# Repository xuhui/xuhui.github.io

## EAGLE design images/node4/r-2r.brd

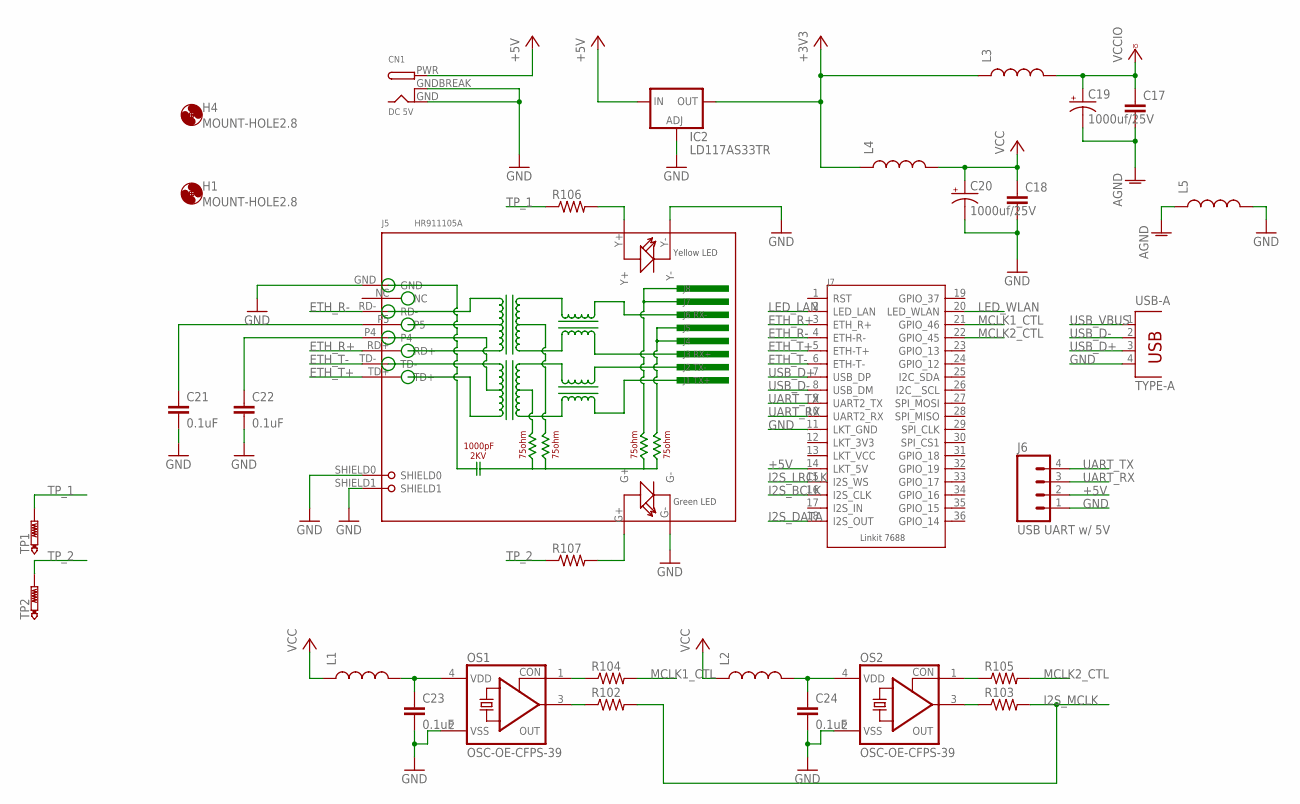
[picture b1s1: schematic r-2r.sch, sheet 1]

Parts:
C17, C18: CAPPTH1; CAP-PTH-5MM
C19, C20: 1000uf/25V; CPOL-RADIAL-1000UF-25V-KIT
C21, C22, C23, C24: 0.1uF; 0603-CAP
CN1: DC 5V; DCJACK_2MM_PTH
H1, H4: MOUNT-HOLE2.8; 2,8
IC2: LD117AS33TR; SOT223
J5: HR911105A; RJ45-12+2P-21.3X16.04X13.4MM
J6: USB UART w/ 5V; 1X04
J7: LINKIT-7688; LINKIT-7688-2X18
L1, L2, L5: INDUCTOR0603; 0603
L3, L4: INDUCTORAXIAL-0.6; AXIAL-0.6
OS1, OS2: OSC-OE-CFPS-39; 3.4X2.7-4-PAD
R102, R103, R104, R105, R106, R107: RESISTOR0603-RES; 0603-RES
TP1, TP2: PTR1PAD1-13; P1-13
USB-A: TYPE-A; PN87520

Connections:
+3V3: IC2.4 (OUT), L3.P$1 (1), L4.P$1 (1)
+5V: CN1.PWR, IC2.3 (IN), J6.2, J7.14 (LKT_5V)
AGND: C17.2, C19.-, L5.1; also elsewhere on the board
ETH_R+: J5.RD+, J7.3 (ETH_R+)
ETH_R-: J5.RD-, J7.4 (ETH-R-)
ETH_T+: J5.TD+, J7.5 (ETH-T+)
ETH_T-: J5.TD-, J7.6 (ETH-T-)
GND: C18.2, C20.-, C21.2, C22.2, C23.2, C24.2, CN1.GND, CN1.GNDBREAK, IC2.1 (ADJ), J5.G-, J5.GND, J5.SHIELD0, J5.SHIELD1, J5.Y-, J6.1, J7.11 (LKT_GND), L5.2, OS1.2 (VSS), OS2.2 (VSS), USB-A.4; also elsewhere on the board
I2S_BCLK: J7.16 (I2S_CLK); also elsewhere on the board
I2S_DATA: J7.18 (I2S_OUT); also elsewhere on the board
I2S_LRCLK: J7.15 (I2S_WS); also elsewhere on the board
I2S_MCLK: R102.2, R103.2; also elsewhere on the board
LED_LAN: J7.2 (LED_LAN)
LED_WLAN: J7.20 (LED_WLAN)
MCLK1_CTL: J7.21 (GPIO_46), R104.2
MCLK2_CTL: J7.22 (GPIO_45), R105.2
unnamed: C24.1, L2.2, OS2.4 (VDD)
unnamed: OS2.3 (OUT), R103.1
unnamed: OS1.3 (OUT), R102.1
unnamed: OS1.1 (CON), R104.1
unnamed: OS2.1 (CON), R105.1
unnamed: C23.1, L1.2, OS1.4 (VDD)
unnamed: J5.G+, R107.2
unnamed: J5.Y+, R106.2
unnamed: C22.1, J5.P4
unnamed: C21.1, J5.P5
TP_1: R106.1, TP1.TP
TP_2: R107.1, TP2.TP
UART_RX: J6.3, J7.10 (UART2_RX)
UART_TX: J6.4, J7.9 (UART2_TX)
USB_D+: J7.7 (USB_DP), USB-A.3
USB_D-: J7.8 (USB_DM), USB-A.2
USB_VBUS: USB-A.1
VCC: C18.1, C20.+, L1.1, L2.1, L4.P$2 (2); also elsewhere on the board
VCCIO: C17.1, C19.+, L3.P$2 (2); also elsewhere on the board

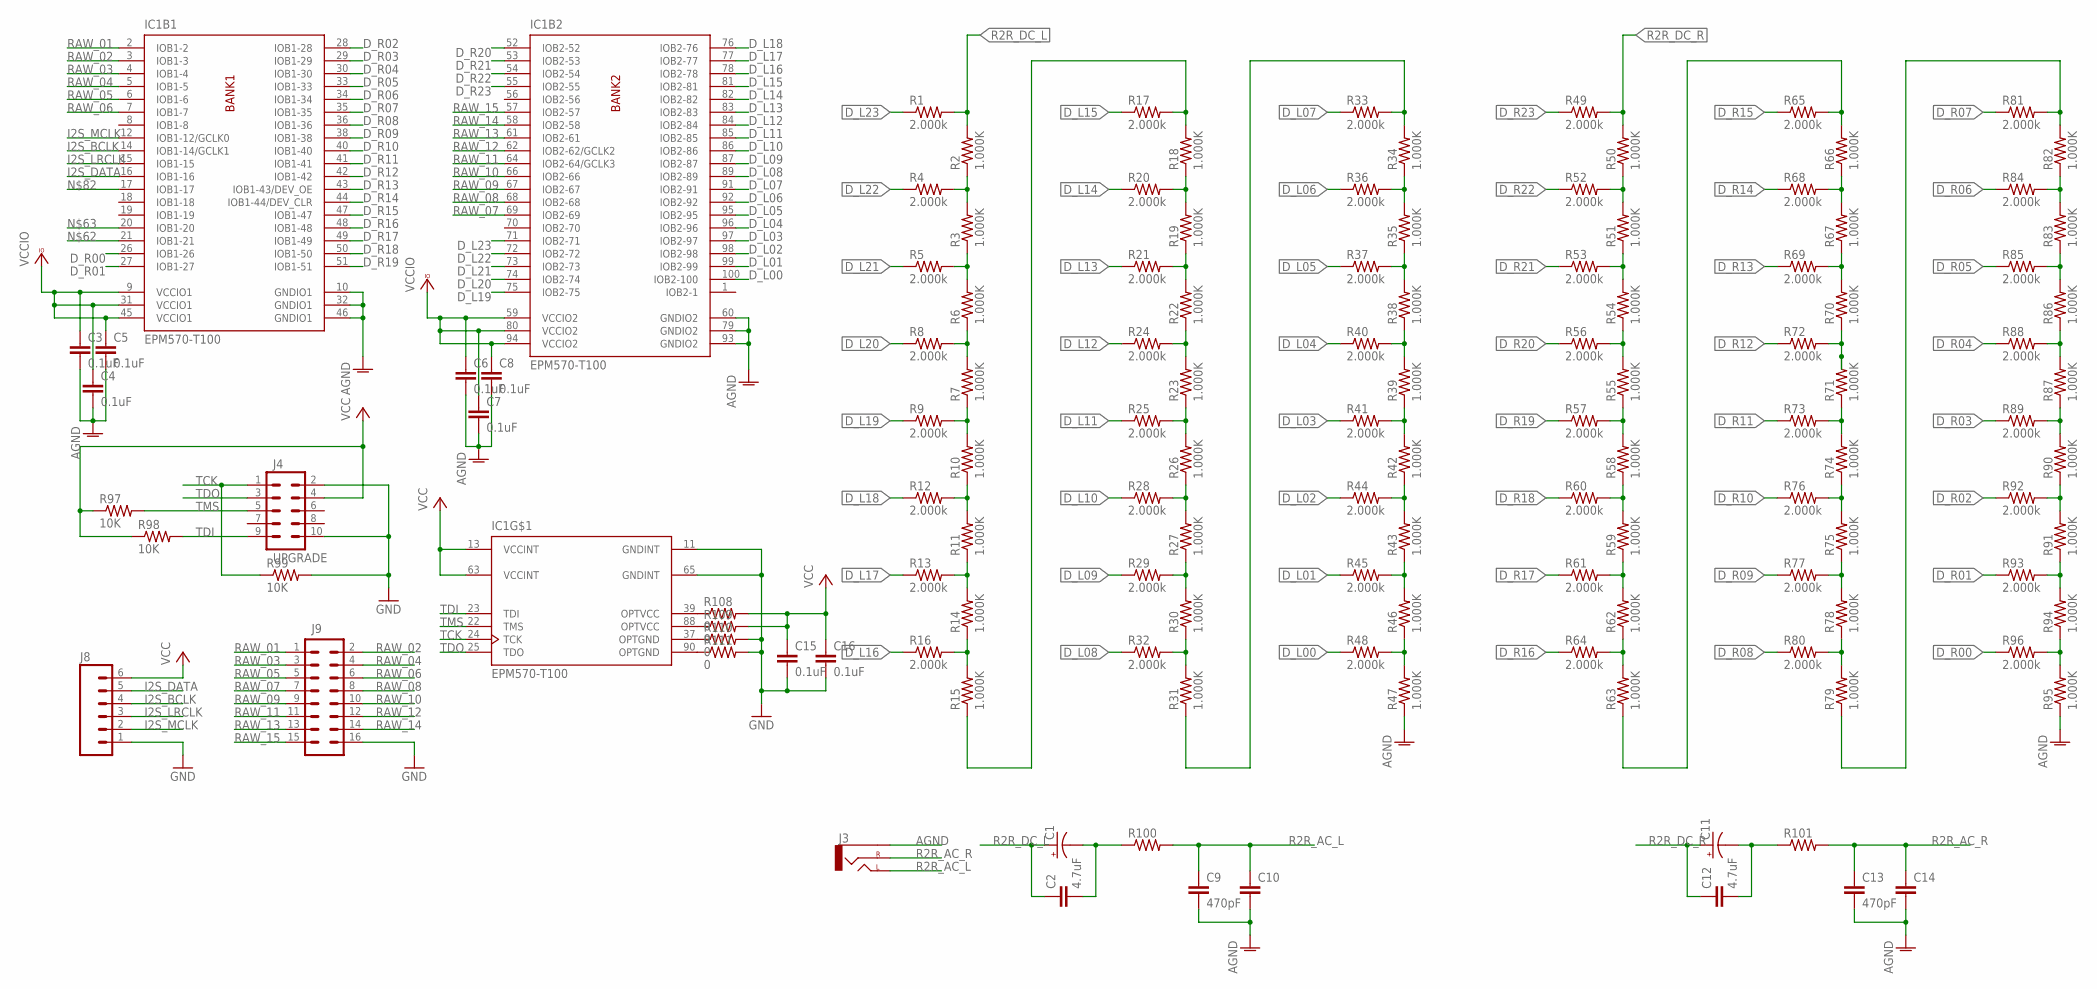
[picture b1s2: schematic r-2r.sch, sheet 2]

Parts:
C1, C11: 10UF-25V-20%(PTH)KIT; CPOL-RADIAL-10UF-25V-KIT
C2, C12: 4.7uF; 1206-CAP
C3, C4, C5, C6, C7, C8, C15, C16: 0.1uF; 0603-CAP
C9, C13: 470pF; 0603-CAP
C10, C14: CAPPTH1; CAP-PTH-5MM
IC1: EPM570-T100; TQFP100
J3: AUDIO-JACKSMD2; AUDIO-JACK-3.5MM-SMD
J4: UPGRADE; 2X5-SHROUDED
J8: M06SILK_FEMALE_PTH; 1X06
J9: M08X2; 2X8
R1, R4, R5, R8, R9, R12, R13, R16, R17, R20, R21, R24, R25, R28, R29, R32, R33, R36, R37, R40, R41, R44, R45, R48, R49, R52, R53, R56, R57, R60, R61, R64, R65, R68, R69, R72, R73, R76, R77, R80, R81, R84, R85, R88, R89, R92, R93, R96: 2.000k; 0603-RES
R2, R3, R6, R7, R10, R11, R14, R15, R18, R19, R22, R23, R26, R27, R30, R31, R34, R35, R38, R39, R42, R43, R46, R47, R50, R51, R54, R55, R58, R59, R62, R63, R66, R67, R70, R71, R74, R75, R78, R79, R82, R83, R86, R87, R90, R91, R94, R95: 1.000K; 0603-RES
R97, R98, R99: 10K; 0603-RES
R100, R101: RESISTOR1206; 1206
R108, R109, R110, R111: 0; 0603

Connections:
AGND: C3.2, C4.2, C5.2, C6.2, C7.2, C8.2, C9.2, C10.2, C13.2, C14.2, IC1.10 (GNDIO1), IC1.32 (GNDIO1), IC1.46 (GNDIO1), IC1.60 (GNDIO2), IC1.79 (GNDIO2), IC1.93 (GNDIO2), J3.SLEEVE, R47.1, R95.1; also elsewhere on the board
D_L00: IC1.100 (IOB2-100), R48.1
D_L01: IC1.99 (IOB2-99), R45.1
D_L02: IC1.98 (IOB2-98), R44.1
D_L03: IC1.97 (IOB2-97), R41.1
D_L04: IC1.96 (IOB2-96), R40.1
D_L05: IC1.95 (IOB2-95), R37.1
D_L06: IC1.92 (IOB2-92), R36.1
D_L07: IC1.91 (IOB2-91), R33.1
D_L08: IC1.89 (IOB2-89), R32.1
D_L09: IC1.87 (IOB2-87), R29.1
D_L10: IC1.86 (IOB2-86), R28.1
D_L11: IC1.85 (IOB2-85), R25.1
D_L12: IC1.84 (IOB2-84), R24.1
D_L13: IC1.83 (IOB2-83), R21.1
D_L14: IC1.82 (IOB2-82), R20.1
D_L15: IC1.81 (IOB2-81), R17.1
D_L16: IC1.78 (IOB2-78), R16.1
D_L17: IC1.77 (IOB2-77), R13.1
D_L18: IC1.76 (IOB2-76), R12.1
D_L19: IC1.75 (IOB2-75), R9.1
D_L20: IC1.74 (IOB2-74), R8.1
D_L21: IC1.73 (IOB2-73), R5.1
D_L22: IC1.72 (IOB2-72), R4.1
D_L23: IC1.71 (IOB2-71), R1.1
D_R00: IC1.26 (IOB1-26), R96.1
D_R01: IC1.27 (IOB1-27), R93.1
D_R02: IC1.28 (IOB1-28), R92.1
D_R03: IC1.29 (IOB1-29), R89.1
D_R04: IC1.30 (IOB1-30), R88.1
D_R05: IC1.33 (IOB1-33), R85.1
D_R06: IC1.34 (IOB1-34), R84.1
D_R07: IC1.35 (IOB1-35), R81.1
D_R08: IC1.36 (IOB1-36), R80.1
D_R09: IC1.38 (IOB1-38), R77.1
D_R10: IC1.40 (IOB1-40), R76.1
D_R11: IC1.41 (IOB1-41), R73.1
D_R12: IC1.42 (IOB1-42), R72.1
D_R13: IC1.43 (IOB1-43/DEV_OE), R69.1
D_R14: IC1.44 (IOB1-44/DEV_CLR), R68.1
D_R15: IC1.47 (IOB1-47), R65.1
D_R16: IC1.48 (IOB1-48), R64.1
D_R17: IC1.49 (IOB1-49), R61.1
D_R18: IC1.50 (IOB1-50), R60.1
D_R19: IC1.51 (IOB1-51), R57.1
D_R20: IC1.52 (IOB2-52), R56.1
D_R21: IC1.53 (IOB2-53), R53.1
D_R22: IC1.54 (IOB2-54), R52.1
D_R23: IC1.55 (IOB2-55), R49.1
GND: C15.2, C16.2, IC1.11 (GNDINT), IC1.65 (GNDINT), J4.2, J4.10, J8.1, J9.16, R99.2, R110.2, R111.2; also elsewhere on the board
I2S_BCLK: IC1.14 (IOB1-14/GCLK1), J8.4; also elsewhere on the board
I2S_DATA: IC1.16 (IOB1-16), J8.5; also elsewhere on the board
I2S_LRCLK: IC1.15 (IOB1-15), J8.3; also elsewhere on the board
I2S_MCLK: IC1.12 (IOB1-12/GCLK0), J8.2; also elsewhere on the board
unnamed: R7.1, R9.2, R10.2
unnamed: R2.1, R3.2, R4.2
unnamed: R3.1, R5.2, R6.2
unnamed: R6.1, R7.2, R8.2
unnamed: C1.2 (-), C2.2, R100.1
unnamed: R10.1, R11.2, R12.2
unnamed: R11.1, R13.2, R14.2
unnamed: R14.1, R15.2, R16.2
unnamed: R15.1, R17.2, R18.2
unnamed: R31.1, R33.2, R34.2
unnamed: R79.1, R81.2, R82.2
unnamed: R63.1, R65.2, R66.2
unnamed: IC1.39 (OPTVCC), R108.1
unnamed: R18.1, R19.2, R20.2
unnamed: R19.1, R21.2, R22.2
unnamed: R46.1, R47.2, R48.2
unnamed: R43.1, R45.2, R46.2
unnamed: R34.1, R35.2, R36.2
unnamed: R35.1, R37.2, R38.2
unnamed: R38.1, R39.2, R40.2
unnamed: R39.1, R41.2, R42.2
unnamed: R42.1, R43.2, R44.2
unnamed: R66.1, R67.2, R68.2
unnamed: R67.1, R69.2, R70.2
unnamed: R70.1, R71.2, R72.2
unnamed: R71.1, R73.2, R74.2
unnamed: R74.1, R75.2, R76.2
unnamed: R75.1, R77.2, R78.2
unnamed: R78.1, R79.2, R80.2
unnamed: R82.1, R83.2, R84.2
unnamed: R83.1, R85.2, R86.2
unnamed: R86.1, R87.2, R88.2
unnamed: R87.1, R89.2, R90.2
unnamed: R90.1, R91.2, R92.2
unnamed: R91.1, R93.2, R94.2
unnamed: R94.1, R95.2, R96.2
unnamed: C11.2 (-), C12.2, R101.1
unnamed: R22.1, R23.2, R24.2
unnamed: R23.1, R25.2, R26.2
unnamed: R26.1, R27.2, R28.2
unnamed: R27.1, R29.2, R30.2
unnamed: R30.1, R31.2, R32.2
unnamed: R50.1, R51.2, R52.2
unnamed: R51.1, R53.2, R54.2
unnamed: R54.1, R55.2, R56.2
unnamed: R55.1, R57.2, R58.2
unnamed: R58.1, R59.2, R60.2
unnamed: R59.1, R61.2, R62.2
unnamed: R62.1, R63.2, R64.2
unnamed: IC1.88 (OPTVCC), R109.1
unnamed: IC1.37 (OPTGND), R110.1
unnamed: IC1.90 (OPTGND), R111.1
R2R_AC_L: C9.1, C10.1, J3.TIP (LEFT), R100.2
R2R_AC_R: C13.1, C14.1, J3.RING (RIGHT), R101.2
R2R_DC_L: C1.1 (+), C2.1, R1.2, R2.2
R2R_DC_R: C11.1 (+), C12.1, R49.2, R50.2
RAW_01: IC1.2 (IOB1-2), J9.1
RAW_02: IC1.3 (IOB1-3), J9.2
RAW_03: IC1.4 (IOB1-4), J9.3
RAW_04: IC1.5 (IOB1-5), J9.4
RAW_05: IC1.6 (IOB1-6), J9.5
RAW_06: IC1.7 (IOB1-7), J9.6
RAW_07: IC1.69 (IOB2-69), J9.7
RAW_08: IC1.68 (IOB2-68), J9.8
RAW_09: IC1.67 (IOB2-67), J9.9
RAW_10: IC1.66 (IOB2-66), J9.10
RAW_11: IC1.64 (IOB2-64/GCLK3), J9.11
RAW_12: IC1.62 (IOB2-62/GCLK2), J9.12
RAW_13: IC1.61 (IOB2-61), J9.13
RAW_14: IC1.58 (IOB2-58), J9.14
RAW_15: IC1.57 (IOB2-57), J9.15
TCK: IC1.24 (TCK), J4.1, R99.1
TDI: IC1.23 (TDI), J4.9, R98.2
TDO: IC1.25 (TDO), J4.3
TMS: IC1.22 (TMS), J4.5, R97.2
VCC: C15.1, C16.1, IC1.13 (VCCINT), IC1.63 (VCCINT), J4.4, J8.6, R97.1, R98.1, R108.2, R109.2; also elsewhere on the board
VCCIO: C3.1, C4.1, C5.1, C6.1, C7.1, C8.1, IC1.9 (VCCIO1), IC1.31 (VCCIO1), IC1.45 (VCCIO1), IC1.59 (VCCIO2), IC1.80 (VCCIO2), IC1.94 (VCCIO2); also elsewhere on the board

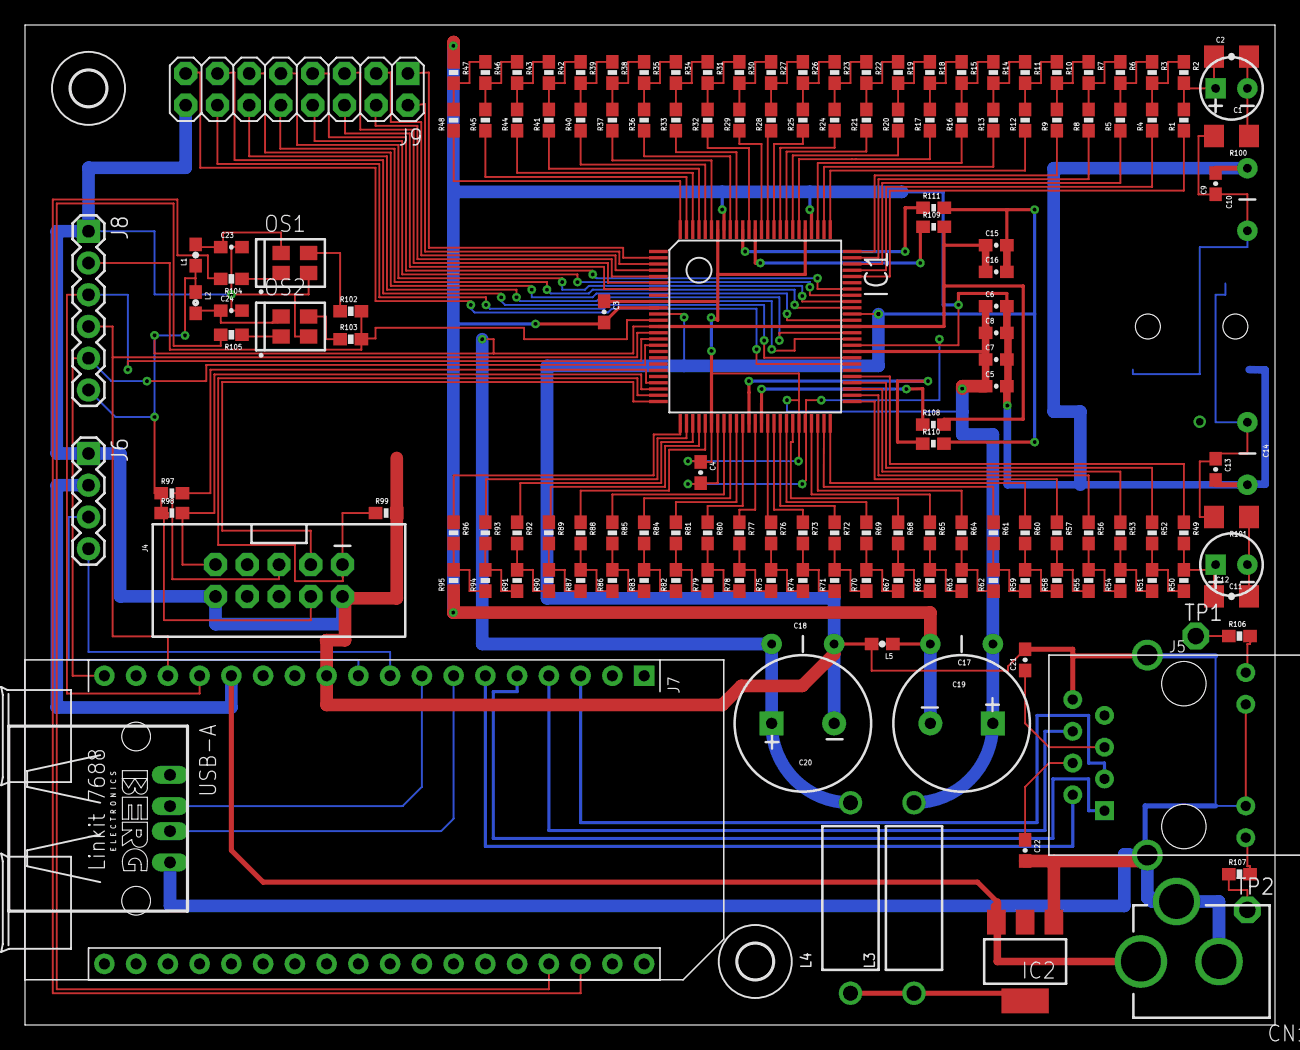
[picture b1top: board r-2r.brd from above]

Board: 2 copper layers, 100.0 x 80.0 mm, 157 parts (1 on the bottom side), 155 nets.

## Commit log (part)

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2016-07-18 update to new template
2016-07-18 forgot Procfile for heroku
2016-07-18 heroku not work, see the log and try add favicon.ico
2016-07-18 try set ruby version
2016-07-18 try ruby 2.2.4 on heroku
2016-07-18 update gem and test heroku again
2016-07-18 heroku works finally, and typo fix
2016-07-18 typo fix
2016-07-18 change Other to More
2016-07-19 fixed navigation and year group, see develop-note.txt for details
2016-07-19 editing
2016-07-19 update picture width
2016-10-20 typo fixing
2016-10-21 update drafts
2016-12-28 update about
2017-01-03 added draft
2017-01-04 update draft
2017-02-12 added capistrano, not config yet
2017-02-12 looks work, with ugly chmod 777, should use setfacl ??
2017-02-12 added note
2017-02-15 added post, and publish one from draft
2017-02-27 added "Why Git is Better than X"
2017-02-27 default expand
2017-02-27 removed ALi in _config, hid about.html from intro
2017-05-07 fixed image url
2017-05-12 added canvas-net(https://github.com/hustcc/canvas-nest.js/blob/master/README-zh.md)
2017-09-12 added fork.txt
2017-09-12 remove canvas.js, update logo picture
2017-09-18 added images
2019-02-03 update Gemfile
2019-03-15 update post
2019-07-16 resize picture for fast load
2019-07-18 update post, and resize the pictures for faster loading
2019-07-19 added pictures, update post
2019-10-14 added reveal.js @ bef2722
2019-10-14 clean up
2019-10-14 improved the slides.html page, sort item by date reversed
2019-10-14 not to show default slide title
2019-12-11 added slides
2019-12-11 keep the sample file
2019-12-11 Bump js-yaml from 3.13.0 to 3.13.1 in /libs/reveal.js/3.8.0
    Bumps [js-yaml](https://github.com/nodeca/js-yaml) from 3.13.0 to 3.13.1.
    - [Release notes](https://github.com/nodeca/js-yaml/releases)
    - [Changelog](https://github.com/nodeca/js-yaml/blob/master/CHANGELOG.md)
    - [Commits](https://github.com/nodeca/js-yaml/compare/3.13.0...3.13.1)
2019-12-11 Bump tar from 2.2.1 to 2.2.2 in /libs/reveal.js/3.8.0
    Bumps [tar](https://github.com/npm/node-tar) from 2.2.1 to 2.2.2.
    - [Release notes](https://github.com/npm/node-tar/releases)
    - [Commits](https://github.com/npm/node-tar/compare/v2.2.1...v2.2.2)
2019-12-11 Bump lodash from 4.17.11 to 4.17.15 in /libs/reveal.js/3.8.0
    Bumps [lodash](https://github.com/lodash/lodash) from 4.17.11 to 4.17.15.
    - [Release notes](https://github.com/lodash/lodash/releases)
    - [Commits](https://github.com/lodash/lodash/compare/4.17.11...4.17.15)
2019-12-11 Bump fstream from 1.0.11 to 1.0.12 in /libs/reveal.js/3.8.0
    Bumps [fstream](https://github.com/npm/fstream) from 1.0.11 to 1.0.12.
    - [Release notes](https://github.com/npm/fstream/releases)
    - [Commits](https://github.com/npm/fstream/compare/v1.0.11...v1.0.12)
2019-12-11 update slides
2019-12-28 update nav bar
2020-02-07 update CNAME
2020-02-07 re-org blogs
2020-02-07 clean categories
2020-02-19 add a note.html page which not list in index page, for personal use
2020-02-26 Bump nokogiri from 1.10.3 to 1.10.8
    Bumps [nokogiri](https://github.com/sparklemotion/nokogiri) from 1.10.3 to 1.10.8.
    - [Release notes](https://github.com/sparklemotion/nokogiri/releases)
    - [Changelog](https://github.com/sparklemotion/nokogiri/blob/master/CHANGELOG.md)
    - [Commits](https://github.com/sparklemotion/nokogiri/compare/v1.10.3...v1.10.8)
2020-04-16 Bump https-proxy-agent from 2.2.1 to 2.2.4 in /libs/reveal.js/3.8.0
    Bumps [https-proxy-agent](https://github.com/TooTallNate/node-https-proxy-agent) from 2.2.1 to 2.2.4.
    - [Release notes](https://github.com/TooTallNate/node-https-proxy-agent/releases)
    - [Commits](https://github.com/TooTallNate/node-https-proxy-agent/compare/2.2.1...2.2.4)
2020-06-07 Bump websocket-extensions from 0.1.3 to 0.1.4 in /libs/reveal.js/3.8.0
    Bumps [websocket-extensions](https://github.com/faye/websocket-extensions-node) from 0.1.3 to 0.1.4.
    - [Release notes](https://github.com/faye/websocket-extensions-node/releases)
    - [Changelog](https://github.com/faye/websocket-extensions-node/blob/master/CHANGELOG.md)
    - [Commits](https://github.com/faye/websocket-extensions-node/compare/0.1.3...0.1.4)
2020-07-03 added and update page/post/slide
2020-07-29 added simple page protect, add slides
2020-07-29 Bump nokogiri from 1.10.3 to 1.10.10
    Bumps [nokogiri](https://github.com/sparklemotion/nokogiri) from 1.10.3 to 1.10.10.
    - [Release notes](https://github.com/sparklemotion/nokogiri/releases)
    - [Changelog](https://github.com/sparklemotion/nokogiri/blob/master/CHANGELOG.md)
    - [Commits](https://github.com/sparklemotion/nokogiri/compare/v1.10.3...v1.10.10)
2020-07-29 update slide
2020-09-03 Bump puppeteer from 1.12.2 to 1.20.0 in /libs/reveal.js/3.8.0
    Bumps [puppeteer](https://github.com/puppeteer/puppeteer) from 1.12.2 to 1.20.0.
    - [Release notes](https://github.com/puppeteer/puppeteer/releases)
    - [Commits](https://github.com/puppeteer/puppeteer/compare/v1.12.2...v1.20.0)
2020-12-12 Bump ini from 1.3.5 to 1.3.8 in /libs/reveal.js/3.8.0
    Bumps [ini](https://github.com/isaacs/ini) from 1.3.5 to 1.3.8.
    - [Release notes](https://github.com/isaacs/ini/releases)
    - [Commits](https://github.com/isaacs/ini/compare/v1.3.5...v1.3.8)
2021-03-31 Bump y18n from 3.2.1 to 3.2.2 in /libs/reveal.js/3.8.0
    Bumps [y18n](https://github.com/yargs/y18n) from 3.2.1 to 3.2.2.
    - [Release notes](https://github.com/yargs/y18n/releases)
    - [Changelog](https://github.com/yargs/y18n/blob/master/CHANGELOG.md)
    - [Commits](https://github.com/yargs/y18n/commits)
2021-05-07 Bump grunt from 1.0.4 to 1.3.0 in /libs/reveal.js/3.8.0
    Bumps [grunt](https://github.com/gruntjs/grunt) from 1.0.4 to 1.3.0.
    - [Release notes](https://github.com/gruntjs/grunt/releases)
    - [Changelog](https://github.com/gruntjs/grunt/blob/main/CHANGELOG)
    - [Commits](https://github.com/gruntjs/grunt/compare/v1.0.4...v1.3.0)
2021-05-11 Bump hosted-git-info from 2.1.5 to 2.8.9 in /libs/reveal.js/3.8.0
    Bumps [hosted-git-info](https://github.com/npm/hosted-git-info) from 2.1.5 to 2.8.9.
    - [Release notes](https://github.com/npm/hosted-git-info/releases)
    - [Changelog](https://github.com/npm/hosted-git-info/blob/v2.8.9/CHANGELOG.md)
    - [Commits](https://github.com/npm/hosted-git-info/compare/v2.1.5...v2.8.9)
2021-05-20 Bump nokogiri from 1.10.3 to 1.11.5
    Bumps [nokogiri](https://github.com/sparklemotion/nokogiri) from 1.10.3 to 1.11.5.
    - [Release notes](https://github.com/sparklemotion/nokogiri/releases)
    - [Changelog](https://github.com/sparklemotion/nokogiri/blob/main/CHANGELOG.md)
    - [Commits](https://github.com/sparklemotion/nokogiri/compare/v1.10.3...v1.11.5)
2021-07-13 Bump addressable from 2.6.0 to 2.8.0
    Bumps [addressable](https://github.com/sporkmonger/addressable) from 2.6.0 to 2.8.0.
    - [Release notes](https://github.com/sporkmonger/addressable/releases)
    - [Changelog](https://github.com/sporkmonger/addressable/blob/main/CHANGELOG.md)
    - [Commits](https://github.com/sporkmonger/addressable/compare/addressable-2.6.0...addressable-2.8.0)
    ---
    updated-dependencies:
2021-09-27 Bump nokogiri from 1.10.3 to 1.12.5
    Bumps [nokogiri](https://github.com/sparklemotion/nokogiri) from 1.10.3 to 1.12.5.
    - [Release notes](https://github.com/sparklemotion/nokogiri/releases)
    - [Changelog](https://github.com/sparklemotion/nokogiri/blob/main/CHANGELOG.md)
    - [Commits](https://github.com/sparklemotion/nokogiri/compare/v1.10.3...v1.12.5)
    ---
    updated-dependencies:
2022-02-12 Bump ajv from 6.9.2 to 6.12.6 in /libs/reveal.js/3.8.0
    Bumps [ajv](https://github.com/ajv-validator/ajv) from 6.9.2 to 6.12.6.
    - [Release notes](https://github.com/ajv-validator/ajv/releases)
    - [Commits](https://github.com/ajv-validator/ajv/compare/v6.9.2...v6.12.6)
    ---
    updated-dependencies:
    - dependency-name: ajv
2022-02-26 Bump nokogiri from 1.10.3 to 1.13.3
    Bumps [nokogiri](https://github.com/sparklemotion/nokogiri) from 1.10.3 to 1.13.3.
    - [Release notes](https://github.com/sparklemotion/nokogiri/releases)
    - [Changelog](https://github.com/sparklemotion/nokogiri/blob/main/CHANGELOG.md)
    - [Commits](https://github.com/sparklemotion/nokogiri/compare/v1.10.3...v1.13.3)
    ---
    updated-dependencies:
2022-04-27 Bump grunt from 1.0.4 to 1.5.2 in /libs/reveal.js/3.8.0
    Bumps [grunt](https://github.com/gruntjs/grunt) from 1.0.4 to 1.5.2.
    - [Release notes](https://github.com/gruntjs/grunt/releases)
    - [Changelog](https://github.com/gruntjs/grunt/blob/main/CHANGELOG)
    - [Commits](https://github.com/gruntjs/grunt/compare/v1.0.4...v1.5.2)
    ---
    updated-dependencies:
2022-05-18 Bump nokogiri from 1.10.3 to 1.13.6
    Bumps [nokogiri](https://github.com/sparklemotion/nokogiri) from 1.10.3 to 1.13.6.
    - [Release notes](https://github.com/sparklemotion/nokogiri/releases)
    - [Changelog](https://github.com/sparklemotion/nokogiri/blob/main/CHANGELOG.md)
    - [Commits](https://github.com/sparklemotion/nokogiri/compare/v1.10.3...v1.13.6)
    ---
    updated-dependencies:
2022-07-22 Bump tzinfo from 1.2.5 to 1.2.10
    Bumps [tzinfo](https://github.com/tzinfo/tzinfo) from 1.2.5 to 1.2.10.
    - [Release notes](https://github.com/tzinfo/tzinfo/releases)
    - [Changelog](https://github.com/tzinfo/tzinfo/blob/master/CHANGES.md)
    - [Commits](https://github.com/tzinfo/tzinfo/compare/v1.2.5...v1.2.10)
    ---
    updated-dependencies:
2022-10-06 Bump addressable from 2.6.0 to 2.8.1
    Bumps [addressable](https://github.com/sporkmonger/addressable) from 2.6.0 to 2.8.1.
    - [Release notes](https://github.com/sporkmonger/addressable/releases)
    - [Changelog](https://github.com/sporkmonger/addressable/blob/main/CHANGELOG.md)
    - [Commits](https://github.com/sporkmonger/addressable/compare/addressable-2.6.0...addressable-2.8.1)
    ---
    updated-dependencies:
2022-12-05 Bump decode-uri-component from 0.2.0 to 0.2.2 in /libs/reveal.js/3.8.0
    Bumps [decode-uri-component](https://github.com/SamVerschueren/decode-uri-component) from 0.2.0 to 0.2.2.
    - [Release notes](https://github.com/SamVerschueren/decode-uri-component/releases)
    - [Commits](https://github.com/SamVerschueren/decode-uri-component/compare/v0.2.0...v0.2.2)
    ---
    updated-dependencies:
    - dependency-name: decode-uri-component
2022-12-07 Bump express from 4.16.2 to 4.17.3 in /libs/reveal.js/3.8.0
    Bumps [express](https://github.com/expressjs/express) from 4.16.2 to 4.17.3.
    - [Release notes](https://github.com/expressjs/express/releases)
    - [Changelog](https://github.com/expressjs/express/blob/master/History.md)
    - [Commits](https://github.com/expressjs/express/compare/4.16.2...4.17.3)
    ---
    updated-dependencies:
2023-04-23 update Gemfile for testing with ruby 3.2.2-1 (https://rubyinstaller.org/downloads/)
2024-04-07 add plantuml
2024-04-07 'update'
2024-04-08 copy some js to local for fixing access issue
2024-04-09 add/update post, and fixing
2024-04-12 moved post to seperated folder
2024-04-12 added start/stop scripts
2024-04-12 update ignore file
2024-04-15 added ee/sees to nav bar
2024-04-24 added jekyll-mermaid, but runs very very slow.. ref: https://github.com/jasonbellamy/jekyll-mermaid cdn: https://www.jsdelivr.com/package/npm/mermaid
2024-04-24 added/fixed scripts. remove mermaid test
2024-05-07 re-org the nav bar
2024-05-07 copy images from old blog and clean up
2024-07-21 add mermaid / plantuml to slide for test
2024-07-21 keed the drafted slides
2024-07-21 copy test page from: https://github.com/reveal-plantuml/reveal-plantuml.github.io/blob/master/index.html
2024-08-02 added joe talk

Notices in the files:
parts and their libraries:
SparkFun-Connectors: Licensing: Creative Commons ShareAlike 4.0 International - https://creativecommons.org/licenses/by-sa/4.0
